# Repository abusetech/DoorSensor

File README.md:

# DoorSensor

This is a wireless sensor that uses an accelerometer and an NRF24l01+ wireless transceiver to monitor the state of a door thumbturn (The small knob that moves the deadbolt). The sensor physically attaches to the deadbolt and uses the accelerometer to deterimine its orientation and therefore the state of the deadbolt. This allows the device to be attached to the door without modifying the entry or causing damage. This is important in scenarios such as apartment rentals as lease agreements typically do not allow tenants to modify or replace the door lock.

This sensor is battery operated and designed to have very low power comsumption in order to allow the batteries to last a long time.

### Project contents

* Circuit schematic (board design coming soon!)
* Firmware sources, including some novel abstractions for the accelerometer and radio
* Arduino code to receive data from the remote sensor (coming soon)
* Testing tools for various parts of the project

### Firmware features

* A tiny, highly optimized software TWI (I2C compatible) implementation
* Firmware code optimized for ultra low power consumption battery powered operation

### Parts

* ATTINY44/84
* ADXL345
* NRF24L01(+) module
* 2x AAA battery holder

You will also need an Arduino board and a second NRF24L01+ to build the receiver.

### Project Plan

The Arduino will run firmware that allows it to connect to HomeAssistant. It acts as a bridge between the HomeAssistant and the wireless sensor.

### Building

Make a build directory:

`$ mkdir build`

Run `make`

`$ make all`

### Debugging

This project can be run in [simavr](https://github.com/buserror/simavr). To do so, build the binaries and then execute the ELF inside simavr:

`$ simavr -g build/attiny44.elf`

Then connect to simavr using gdb:

`avr-gdb -ex "symbol-file build/attiny44.elf" -ex "target remote localhost:1234"`

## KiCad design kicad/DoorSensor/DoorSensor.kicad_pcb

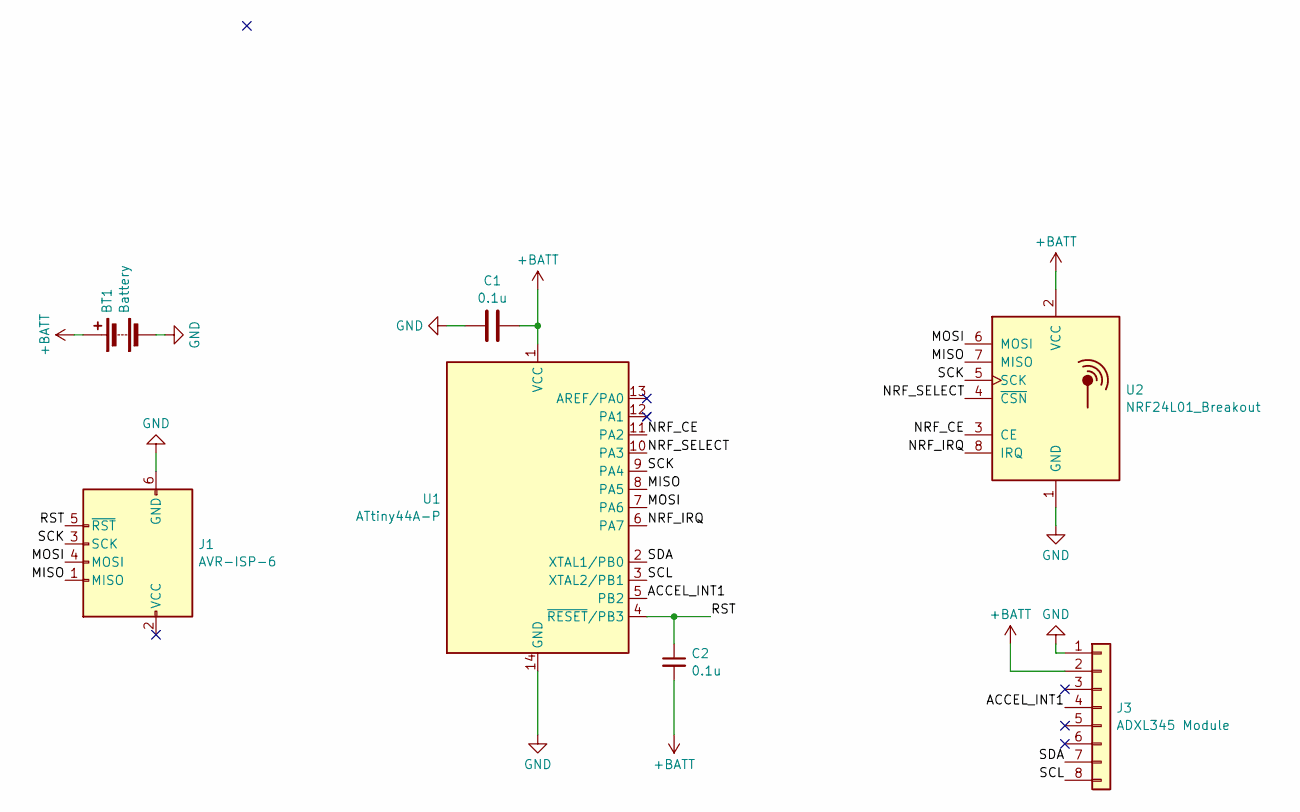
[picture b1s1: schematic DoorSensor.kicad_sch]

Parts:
BT1: Battery; TerminalBlock_4Ucon_1x02_P3.50mm_Horizontal
C1, C2: 0.1u; C_Disc_D4.3mm_W1.9mm_P5.00mm
J1: AVR-ISP-6; IDC-Header_2x03_P2.54mm_Vertical
J3: ADXL345 Module; PinHeader_1x08_P2.54mm_Vertical
U1: ATtiny44A-P; DIP-14_W7.62mm
U2: NRF24L01_Breakout; nRF24L01_Breakout

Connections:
+BATT: BT1.1 (+), C1.2, C2.2, J3.2, U1.1 (VCC), U2.2 (VCC)
/ACCEL_INT1: J3.4, U1.5 (PB2)
/MISO: J1.1 (MISO), U1.8 (PA5), U2.7 (MISO)
/MOSI: J1.4 (MOSI), U1.7 (PA6), U2.6 (MOSI)
/NRF_CE: U1.11 (PA2), U2.3 (CE)
/NRF_IRQ: U1.6 (PA7), U2.8 (IRQ)
/NRF_SELECT: U1.10 (PA3), U2.4 (~CSN)
/RST: C2.1, J1.5 (~RST), U1.4 (~RESET/PB3)
/SCK: J1.3 (SCK), U1.9 (PA4), U2.5 (SCK)
/SCL: J3.8, U1.3 (XTAL2/PB1)
/SDA: J3.7, U1.2 (XTAL1/PB0)
GND: BT1.2 (-), C1.1, J1.6 (GND), J3.1, U1.14 (GND), U2.1 (GND)

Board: 2 copper layers, 7 parts (1 on the bottom side), 12 nets, no tracks yet.

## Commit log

2025-03-13 Makefile; README
2025-03-13 markdown
2025-03-13 typo
2025-03-14 Makefile fixes
2025-03-14 Makefile, fix warnings
2025-03-17 Tests; Software I2C; ADXL345
2025-03-26 SoftI2C: multi-byte write
2025-03-27 SoftI2C::readBytes(); Cleanup
2025-04-02 Fixed memory allocated to _pi in i2cwave test not zeroed; added README for test
2025-04-03 ADXL345 configuration
2025-04-03 read accelerometer value
2025-04-04 simavr support; initial board layout
2025-04-09 Fixed WDT causing resets instead of triggering an interrupt
2025-04-11 Added battery voltage measurement code
2025-04-28 README
